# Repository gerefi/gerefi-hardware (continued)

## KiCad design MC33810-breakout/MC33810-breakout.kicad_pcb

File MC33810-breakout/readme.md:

https://www.nxp.com/products/power-management/smart-switches-and-drivers/low-side-switches/automotive-engine-control-ic:MC33810

https://github.com/gerefi2/hellen-one/issues/173

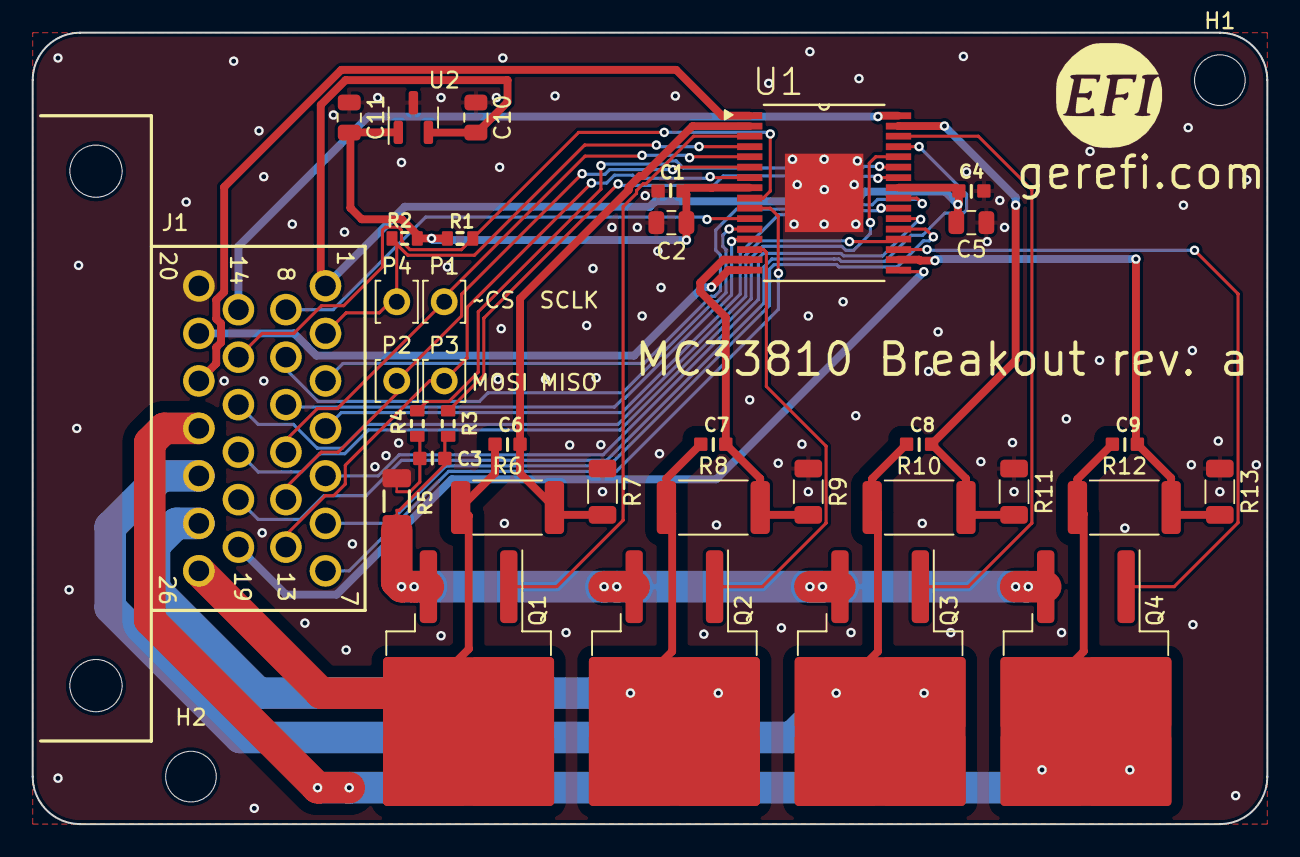
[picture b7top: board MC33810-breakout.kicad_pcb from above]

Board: 2 copper layers, 78.0 x 50.0 mm, 38 parts (0 on the bottom side), 40 nets.

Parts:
C1, C4, C6, C7, C8, C9: 100n; C0603
C2, C5, C10, C11: 10u; C_0805_2012Metric
C3: 100p; C0603
G1: gerefi_LOGO; gerefi_logo
H1, H2: M3; MountingHole_3.2mm_M3_ISO14580
J1: 6473423-1
P1, P2, P3, P4: Pad; PAD-TH
Q1, Q2, Q3, Q4: ISL9V3040S3S; TO-263-2
R1, R2: 10k; R0603
R3, R4: 100; R0603
R5: 0.02; Shunt_1206
R6, R8, R10, R12: 36k; R_2512_6332Metric
R7, R9, R11, R13: 4.02k; R_1206_3216Metric
U1: MCZ33810EK; Mcz33810
U2: XC6202P332MR-G; SOT-23

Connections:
+3.3V: C1.1, C2.2, C11.2, R1.2, R2.2, U1.8 (VDD), U2.1 (VO)
+BATT: C4.1, C5.2, C10.2, J1.1 (1B), U1.25 (VPWR), U2.2 (VI)
/IGN1: J1.3 (3B), U1.24 (GIN0)
/IGN2: J1.4 (4B), U1.23 (GIN1)
/IGN3: J1.5 (5B), U1.22 (GIN2)
/IGN4: J1.6 (6B), U1.21 (GIN3)
/INJ1: J1.7 (7B), U1.10 (DIN0)
/INJ2: J1.8 (8B), U1.11 (DIN1)
/INJ3: J1.9 (9B), U1.12 (DIN2)
/INJ4: J1.10 (10B), U1.13 (DIN3)
/MAXI: J1.18 (18B), U1.29 (MAXI)
/MISO: J1.13 (13B), P3.1, U1.7 (SO)
/MOSI: J1.12 (12B), P2.1, U1.6 (SI)
/NOMI: J1.17 (17B), U1.28 (NOMI)
/OUT_IGN1: C6.1, J1.26 (26B), Q1.2 (C), R6.1
/OUT_IGN2: C7.1, J1.25 (25B), Q2.2 (C), R8.1
/OUT_IGN3: C8.1, J1.24 (24B), Q3.2 (C), R10.1
/OUT_IGN4: C9.1, J1.23 (23B), Q4.2 (C), R12.1
/OUT_INJ1: J1.22 (22B), U1.1 (OUT0)
/OUT_INJ2: J1.21 (21B), U1.16 (OUT1)
/OUT_INJ3: J1.14 (14B), U1.32 (OUT2)
/OUT_INJ4: J1.19 (19B), U1.17 (OUT3)
/SCLK: J1.11 (11B), P1.1, U1.5 (SCLK)
/~CS: J1.2 (2B), P4.1, R2.1, U1.4 (~CS)
/~OUTEN: J1.15 (15B), R1.1, U1.9 (~OUTEN)
/~SPKDUR: J1.16 (16B), U1.20 (~SPKDUR)
GND: C1.2, C2.1, C4.2, C5.1, C10.1, C11.1, J1.20 (20B), R5.4, R7.2, R9.2, R11.2, R13.2, U1.33 (GND), U2.3 (GND)
unnamed: C3.1, R3.2, R5.2
unnamed: C3.2, R4.2, R5.3
unnamed: Q1.3 (E), Q2.3 (E), Q3.3 (E), Q4.3 (E), R5.1
unnamed: Q1.1 (G), U1.3 (GD0)
unnamed: Q2.1 (G), U1.14 (GD1)
unnamed: Q3.1 (G), U1.30 (GD2)
unnamed: Q4.1 (G), U1.19 (GD3)
unnamed: C6.2, R6.2, R7.1, U1.2 (FB0)
unnamed: C7.2, R8.2, R9.1, U1.15 (FB1)
unnamed: C8.2, R10.2, R11.1, U1.31 (FB2)
unnamed: C9.2, R12.2, R13.1, U1.18 (FB3)
unnamed: R4.1, U1.27 (RSN)
unnamed: R3.1, U1.26 (RSP)

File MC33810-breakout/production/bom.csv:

Designator,Footprint,Quantity,Value,LCSC Part #
"C1, C4, C6, C7, C8, C9",C0603,6,100n,C14663
"C10, C11, C2, C5",0805,4,10u,C15850
C3,C0603,1,100p,C14858
G1,gerefi_logo,1,gerefi_LOGO,
"H1, H2",MountingHole_3.2mm_M3_ISO14580,2,M3,
J1,6473423-1,1,6473423-1,
"P1, P2, P3, P4",PAD-TH,4,Pad,
"Q1, Q2, Q3, Q4",TO-263-2,4,ISL9V3040S3S,C898702
"R1, R2",R0603,2,10k,C25804
"R10, R12, R6, R8",2512,4,36k,C474088
"R11, R13, R7, R9",1206,4,4.02k,C274026
"R3, R4",R0603,2,100,C22775
R5,Shunt_1206,1,0.02,C728292
U1,Mcz33810,1,MCZ33810EK,C3192631
U2,SOT-23,1,XC6202P332MR-G,C47374

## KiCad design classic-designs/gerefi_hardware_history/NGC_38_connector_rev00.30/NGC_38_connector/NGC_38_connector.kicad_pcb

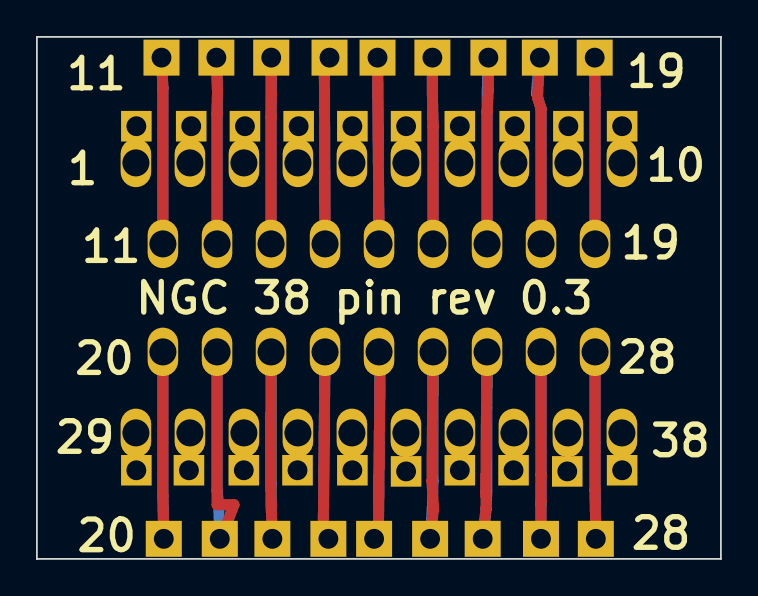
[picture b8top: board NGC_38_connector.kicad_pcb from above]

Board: 2 copper layers, 38.0 x 29.0 mm, 5 parts (0 on the bottom side), 38 nets.

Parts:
P1: DIL38; PCM_C1
P2, P4: CONN_10; SIL-10
P3, P5: CONN_9; SIL-9

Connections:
unnamed: P1.15, P3.5
unnamed: P1.10, P2.10
unnamed: P1.9, P2.9
unnamed: P1.8, P2.8
unnamed: P1.7, P2.7
unnamed: P1.6, P2.6
unnamed: P1.5, P2.5
unnamed: P1.4, P2.4
unnamed: P1.3, P2.3
unnamed: P1.2, P2.2
unnamed: P1.1, P2.1
unnamed: P1.19, P3.9
unnamed: P1.18, P3.8
unnamed: P1.17, P3.7
unnamed: P1.16, P3.6
unnamed: P1.20, P5.1
unnamed: P1.14, P3.4
unnamed: P1.13, P3.3
unnamed: P1.12, P3.2
unnamed: P1.11, P3.1
unnamed: P1.28, P5.9
unnamed: P1.27, P5.8
unnamed: P1.26, P5.7
unnamed: P1.25, P5.6
unnamed: P1.24, P5.5
unnamed: P1.23, P5.4
unnamed: P1.22, P5.3
unnamed: P1.21, P5.2
unnamed: P1.31, P4.3
unnamed: P1.34, P4.6
unnamed: P1.33, P4.5
unnamed: P1.32, P4.4
unnamed: P1.38, P4.10
unnamed: P1.30, P4.2
unnamed: P1.29, P4.1
unnamed: P1.37, P4.9
unnamed: P1.36, P4.8
unnamed: P1.35, P4.7

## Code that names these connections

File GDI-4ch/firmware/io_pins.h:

/*
 * io_pins.h
 *
 * See https://github.com/gerefi/gerefi/tree/master/firmware/config/boards/GDI4/connectors for interactive pinout
 *
 *  Created on: Jan 10, 2022
 */

#pragma once

// D20
#define LED_BLUE_PORT GPIOB
#define LED_BLUE_PIN 13

//wanna develop on blue pill without actual PC2001 connected?
//#define LED_BLUE_PORT GPIOC
//#define LED_BLUE_PIN 13

// D21
#define LED_GREEN_PORT GPIOA
#define LED_GREEN_PIN 8

// Communication - CAN1
#define CAN_GPIO_PORT				GPIOA
#define CAN_TX_PIN				12
#define CAN_RX_PIN				11

// Communication - UART
#define UART_BAUD_RATE      115200

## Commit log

2024-03-19 change
